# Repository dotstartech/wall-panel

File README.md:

# Wall Panel

Wall Panel is a 4-inch wall-mounted touch display panel powered by Raspberry Pi Compute Module 4 (CM4). It features a 720x720 IPS multitouch display and can be used as a Home Assistant dashboard or any other embedded display application.

## Display
We use this [display](https://www.alibaba.com/product-detail/Square-4-Inch-IPS-LCD-Screen_1601268288719.html), but touch variant. It is 4 lane MIPI with i2c touch controller. 
- Display driver: ST7703
- Touch driver: FT6336U

## Possible use cases
- **Home Assistant Dashboard**. Perfect for wall-mounted smart home control panels with full touch interaction and high-resolution display.
- **Information Display**. Show weather, calendar, news, or any other dynamic content in your home or office.
- **Control Panel**. Use as a centralized control interface for IoT devices, lighting, or home automation systems.
- **Embedded Display**. Build custom applications using the full power of Raspberry Pi OS or any Linux distribution on the CM4.

## List of features
- **720x720 IPS Display** with multitouch support
- **Raspberry Pi Compute Module 4** as the main brain
- **External RTC** for accurate timekeeping
- **USB-C** for data and power
- **USB-OTG** support for device mode
- **Action Button** for user interaction
- **WiFi** connectivity
- **40-pin GPIO Header** for Raspberry Pi compatibility
- **SD Card** slot for storage expansion
- **Micro HDMI** output for external displays
- **EEPROM Flashing** capability for firmware updates
- **Backplane Connector** for power and data from the wall and future PoE backplate support

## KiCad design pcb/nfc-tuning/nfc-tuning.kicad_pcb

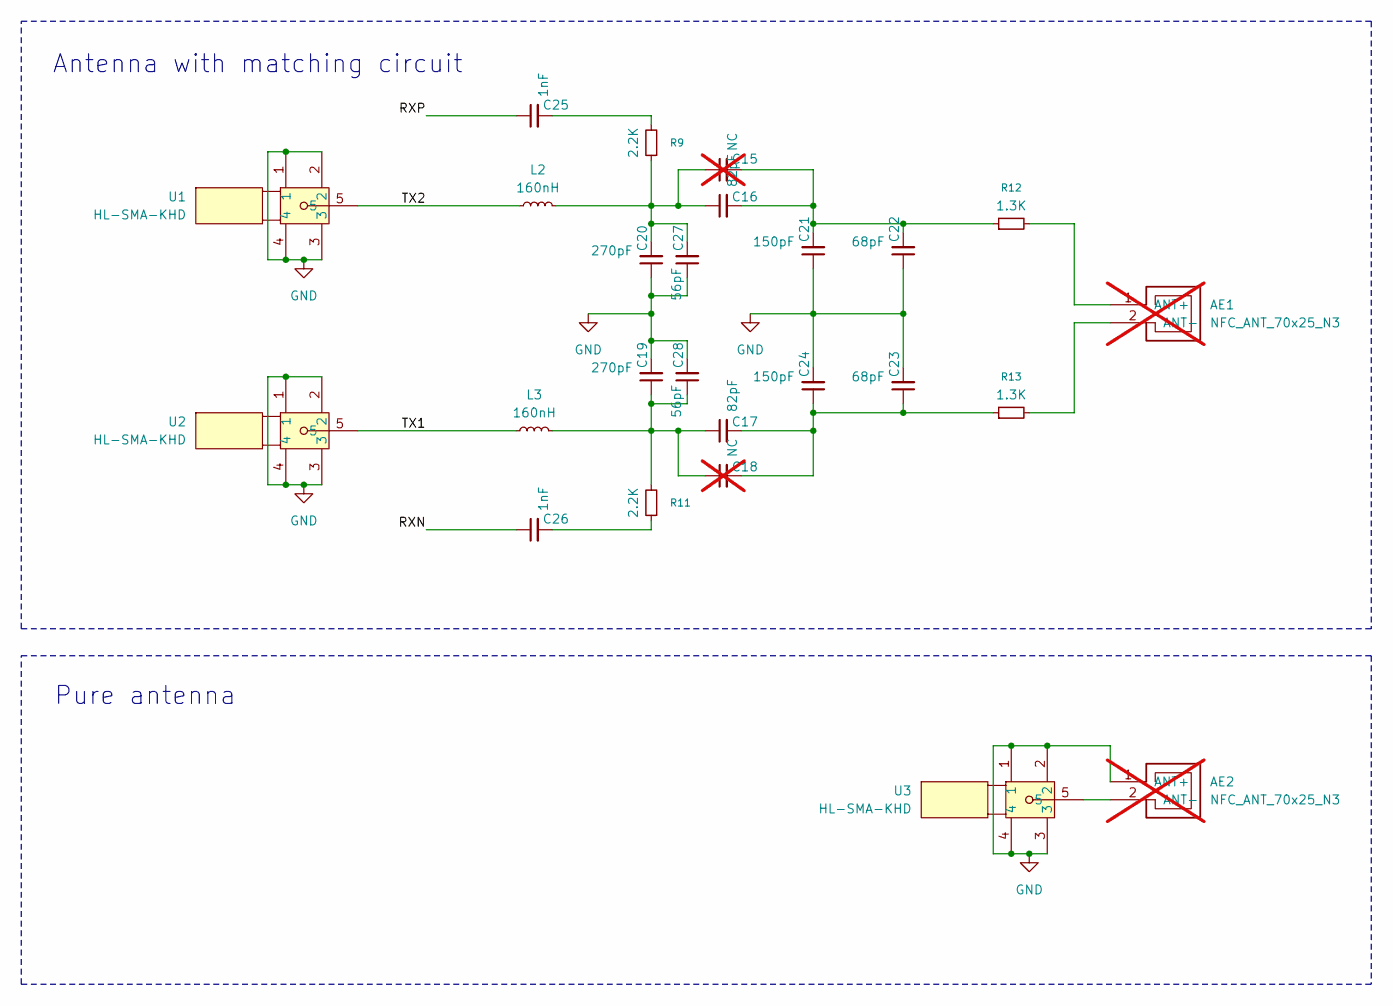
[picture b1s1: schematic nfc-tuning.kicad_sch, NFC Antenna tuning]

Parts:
AE1, AE2: NFC_ANT_70x25_N3; not fitted
C15, C18: NC; C_0402_1005Metric; not fitted
C16, C17: 82pF; C_0402_1005Metric; LCSC C162123
C19, C20: 270pF; C_0402_1005Metric; LCSC C882580
C21, C24: 150pF; C_0402_1005Metric; LCSC C237333
C22, C23: 68pF; C_0402_1005Metric; LCSC C2987942
C25, C26: 1nF; C_0402_1005Metric; LCSC C161523
C27, C28: 56pF; C_0402_1005Metric; LCSC C2189899
L2, L3: 160nH; L_0603_1608Metric; LCSC C437367
R9, R11: 2.2K; R_0402_1005Metric; LCSC C2906865
R12, R13: 1.3K; R_0402_1005Metric; LCSC C185455
U1, U2, U3: HL-SMA-KHD; SMA-TH_HL-SMA-KHD2; MPN HL-SMA-KHD; LCSC Part C19712120

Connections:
/RXN: C26.1
/RXP: C25.1
/TX1: L3.1, U2.5
/TX2: L2.1, U1.5
GND: AE2.1 (ANT+), AE2.2 (ANT-), C19.2, C20.1, C21.1, C22.1, C23.2, C24.2, C27.1, C28.2, U1.1, U1.2, U1.3, U1.4, U2.1, U2.2, U2.3, U2.4, U3.1, U3.2, U3.3, U3.4; also elsewhere on the board
unnamed: AE1.1 (ANT+), R12.2
unnamed: AE1.2 (ANT-), R13.2
unnamed: AE2.2 (ANT-), U3.5
unnamed: C15.1, C16.1, C20.2, C27.2, L2.2, R9.1
unnamed: C15.2, C16.2, C21.2, C22.2, R12.1
unnamed: C17.1, C18.1, C19.1, C28.1, L3.2, R11.2
unnamed: C17.2, C18.2, C23.1, C24.1, R13.1
unnamed: C25.2, R9.2
unnamed: C26.2, R11.1

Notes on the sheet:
Antenna with matching circuit
Pure antenna

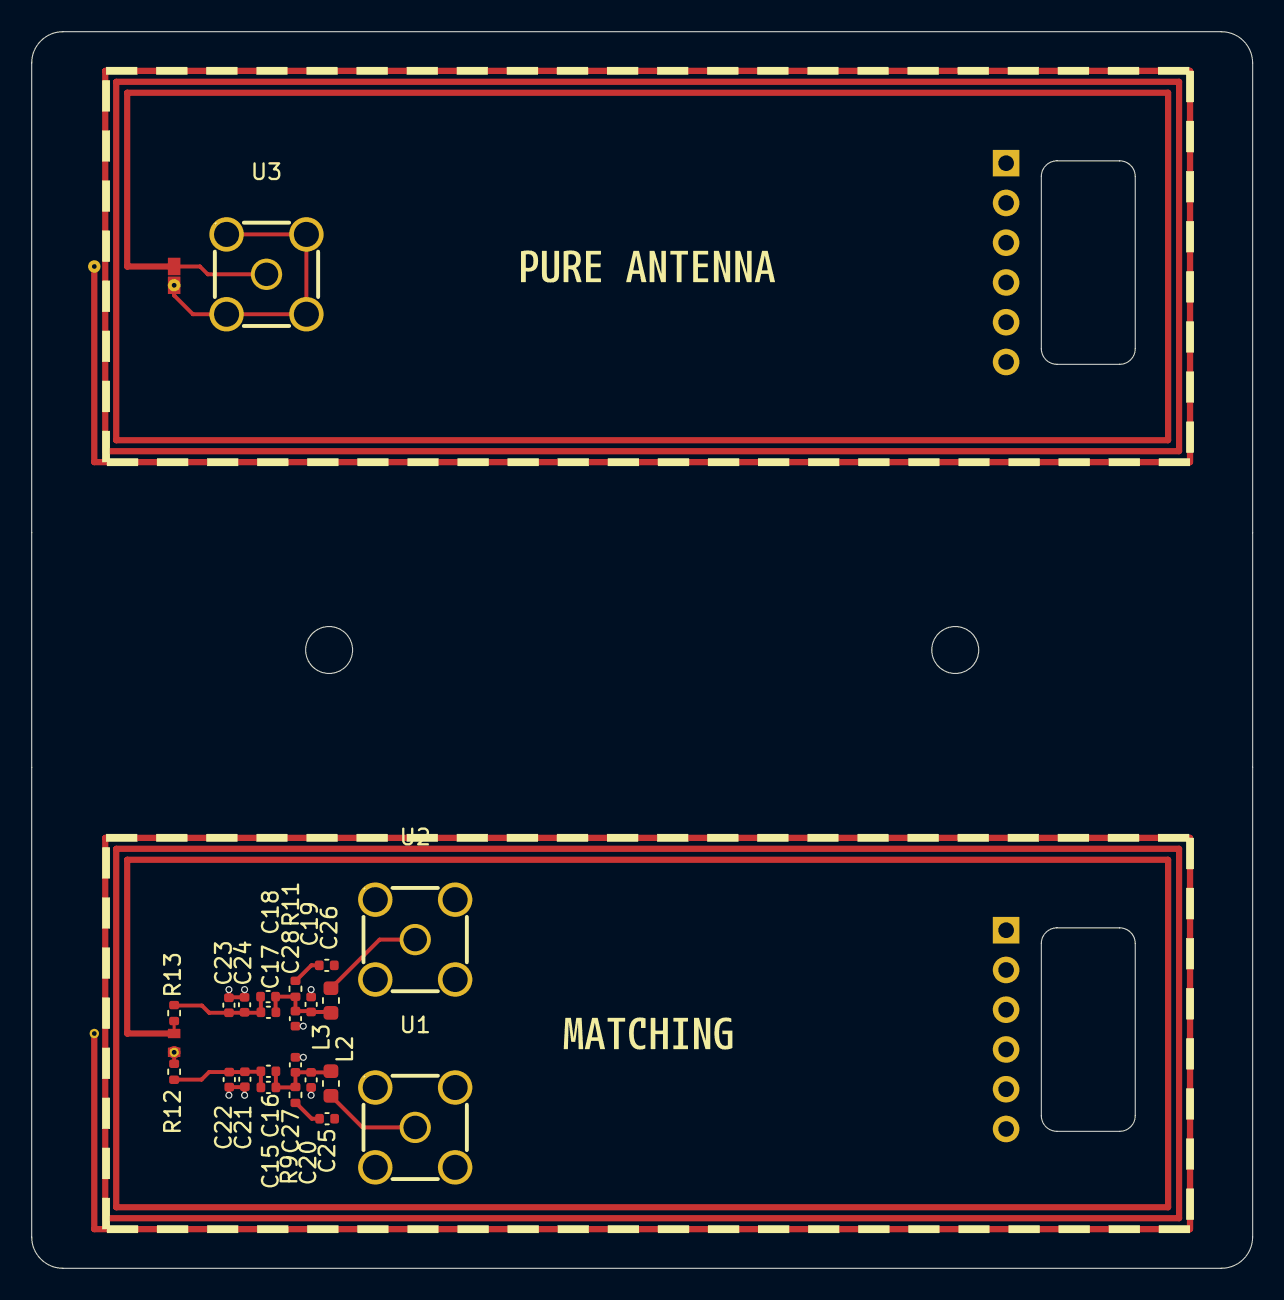
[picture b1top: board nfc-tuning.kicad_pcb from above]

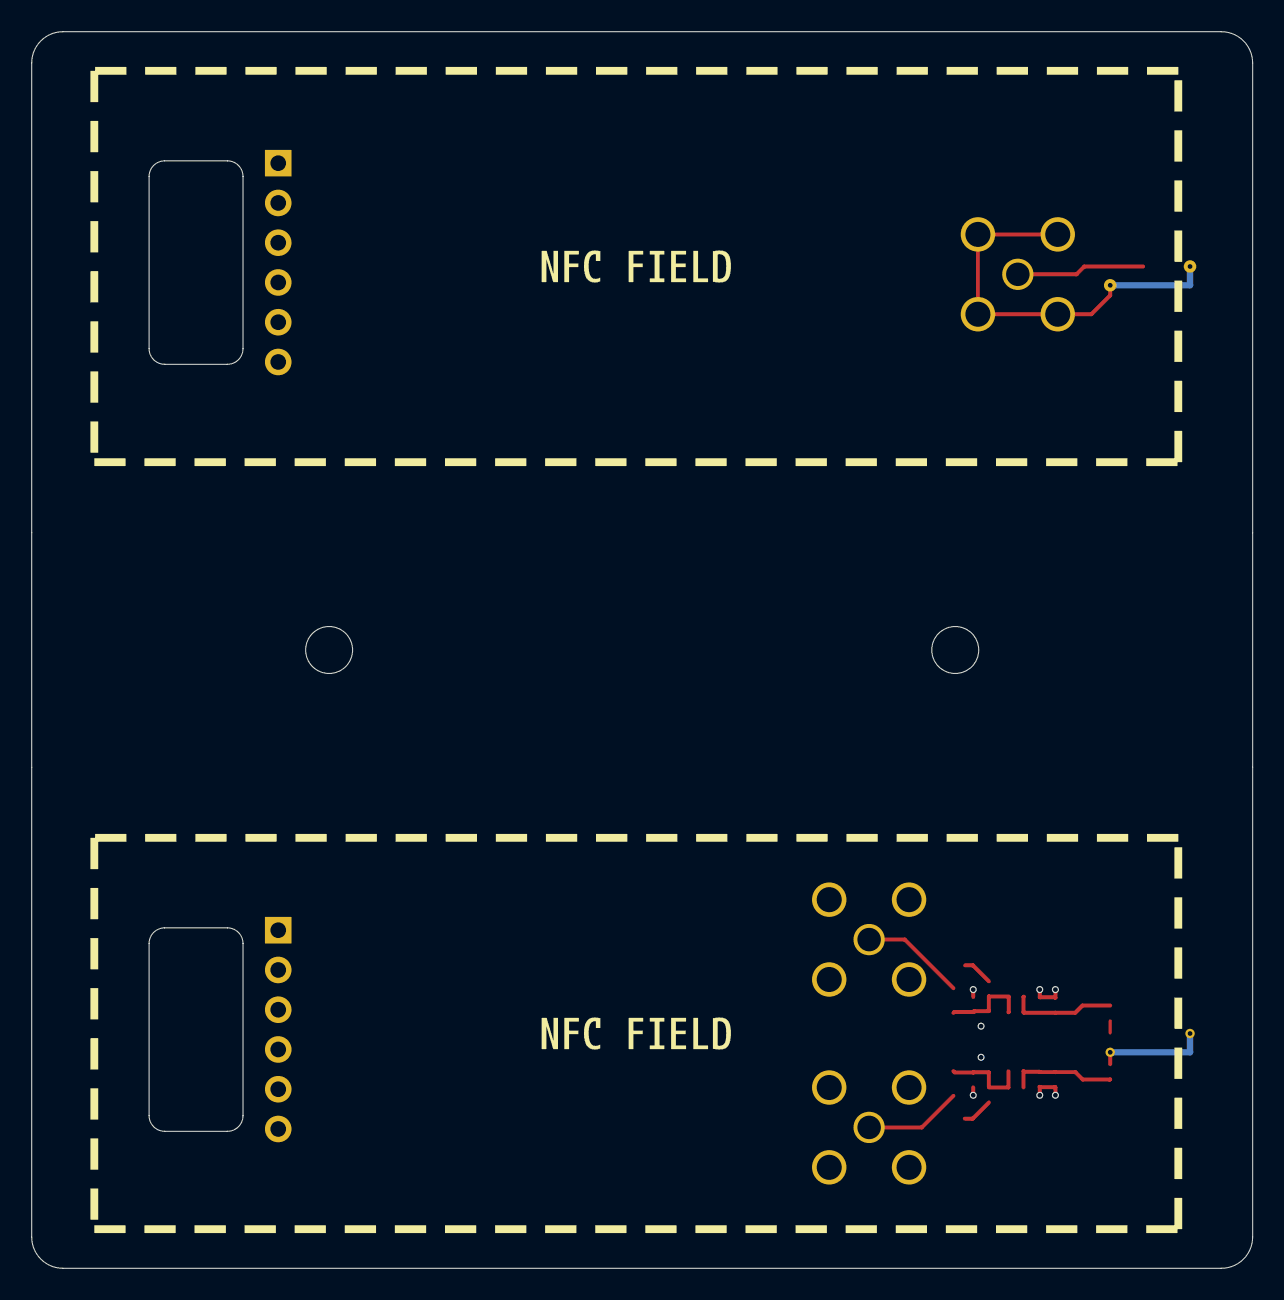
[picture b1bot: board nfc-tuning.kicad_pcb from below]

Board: 4 copper layers, 78.0 x 79.0 mm, 31 parts (2 on the bottom side), 12 nets.

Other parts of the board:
J5, J5#2: Mic Adafruit; SPH0645LM4H
kibuzzard-6A730F68: G***; kibuzzard-6A730F68
kibuzzard-6A730F73: G***; kibuzzard-6A730F73
kibuzzard-6A70487D, kibuzzard-6A70487D#2: G***; kibuzzard-6A70487D

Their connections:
GND: J5#2.2; also elsewhere on the board

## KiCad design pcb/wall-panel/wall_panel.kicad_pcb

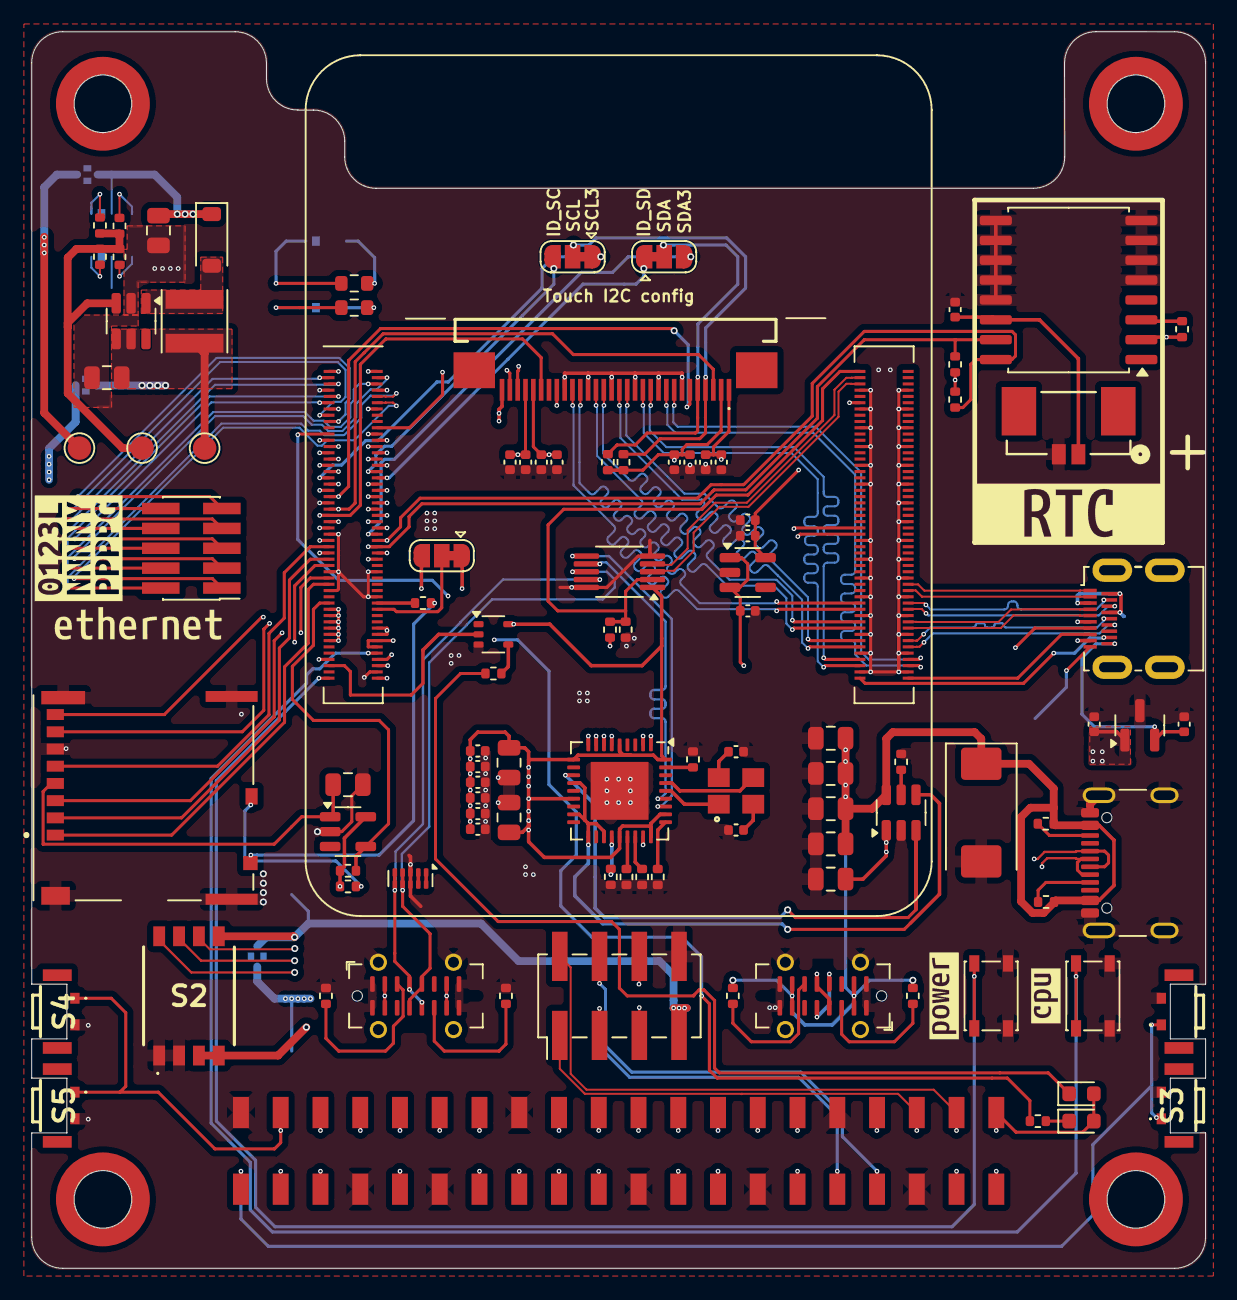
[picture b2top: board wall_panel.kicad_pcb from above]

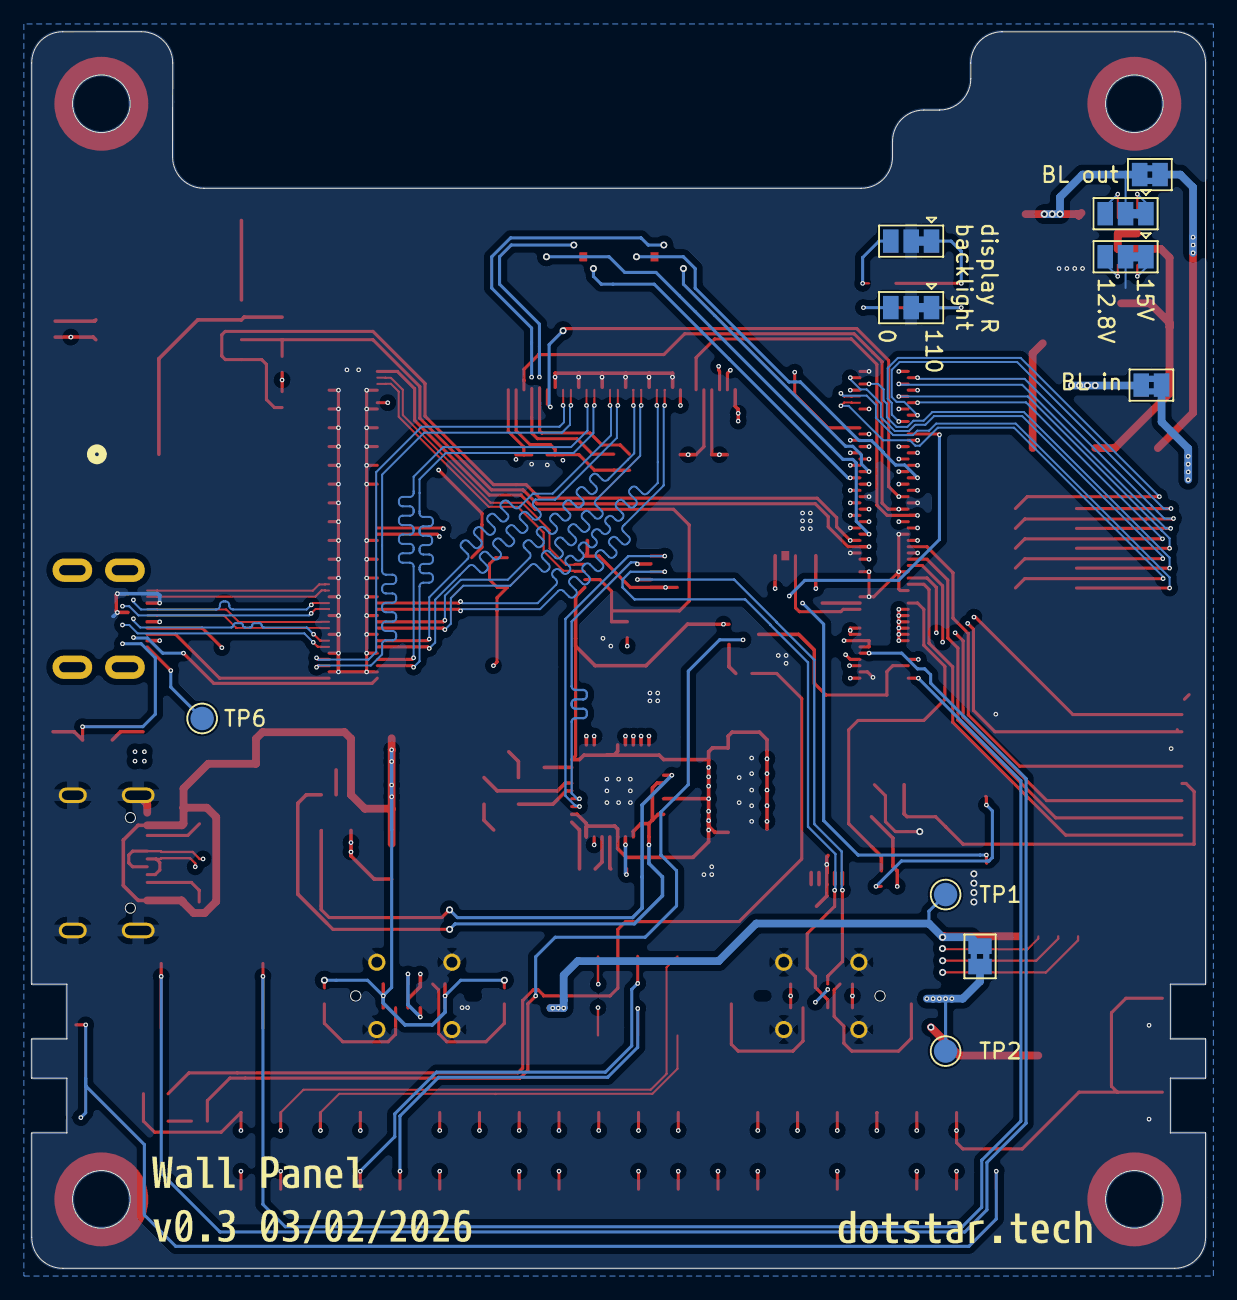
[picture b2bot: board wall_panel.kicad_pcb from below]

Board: 6 copper layers, 75.0 x 79.0 mm, 124 parts (13 on the bottom side), 142 nets.

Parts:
C1, C2: 27pF; C_0402_1005Metric
C3, C4, C11, C13, C14, C15, C16, C31: 10u; C_0805_2012Metric
C5, C6, C7, C8, C9, C10, C17, C18, C19, C22, C23, C24, C27, C28: 100n; C_0402_1005Metric
C12: 100uF; CP_EIA-7343-31_Kemet-D
C20, C21: 10uF; C_0402_1005Metric
C25, C26, C29, C30: 1uF; C_0402_1005Metric
C32, C33: 22uF; C_0805_2012Metric
D1: LED Green; LED_0603_1608Metric
D2: LED Red; LED_0603_1608Metric
D3: B5817W; D_SOD-123
H1, H2, H3, H4: MountingHole_Pad; 9774030151R
J1, J2: USB_C_Receptacle_USB2.0_14P; USB_C_Receptacle_G-Switch_GT-USB-7051x
J4: Conn_01x02_Socket; CONN02_533984002_MOL
J5: SFV30R-4STBE1HLF; SFV30R4STBE1HLF
J6: 690-019-298-412; HDMI_Micro-D_Molex_46765-1x01
J10: THD-20-R; PM254-2-20-WS-8.5
J15: THD-20-R; PinHeader_2x05_P1.27mm_Vertical_SMD
J16: Micro_SD_Card_Det; SDCARD_MOLEX_503398-1892
J17: USB_C_Receptacle_USB2.0_14P; USB_C_Receptacle_GCT_USB4105-xx-A_16P_TopMnt_Horizontal
J18: THD-20-R; PinHeader_2x04_P2.54mm_Vertical_SMD
JP1, JP3, JP4: GPIO reference; SolderJumper-3_P1.3mm_Bridged12_RoundedPad1.0x1.5mm
JP2: Jumper_2_Small_Bridged; SolderJumper-2_P1.3mm_Bridged2Bar_Pad1.0x1.5mm
JP5, JP6: SolderJumper_2_Bridged; SolderJumper-2_P1.3mm_Bridged2Bar_Pad1.0x1.5mm
JP7, JP8: 12.8/15V; SolderJumper-3_P1.3mm_Bridged12_Pad1.0x1.5mm
JP9, JP10: 0/110ohm; SolderJumper-3_P1.3mm_Bridged12_Pad1.0x1.5mm
L1: 10uH; L_Taiyo-Yuden_NR-40xx
Module1: ComputeModule4; Raspberry-Pi-4-Compute-Module
R1, R2, R14, R15: 2.2K 1%; R_0402_1005Metric
R3, R4, R5, R7: 36K 1%; R_0402_1005Metric
R6, R22: 12K 1%; R_0402_1005Metric
R8, R9: 5.1k; R_0402_1005Metric
R10, R12, R25, R26: 56K; R_0402_1005Metric
R11: 15K 1%; R_0402_1005Metric
R13, R18, R29: 10K; R_0402_1005Metric
R16, R19: 1k; R_0402_1005Metric
R17: 200K; R_0402_1005Metric
R20, R21: nf; R_0402_1005Metric
R23, R24: 4.7k; R_0402_1005Metric
R27, R28: 110; R_0603_1608Metric
R30: 240K; R_0402_1005Metric
S1, S3, S4, S5: SKSLLBE010
S2: 218-4LPSTRF; 2184LPSTRF
SW1: power reset; SW_SPST_PTS810
SW2: cpu reset; SW_SPST_PTS810
TP1, TP2, TP6: TestPoint; TestPoint_Pad_D1.5mm
TP3: boost in; TestPoint_Pad_D1.5mm
TP4: boost out; TestPoint_Pad_D1.5mm
TP5: boost fb; TestPoint_Pad_D1.5mm
U1: FSUSB42MUX; MSOP-10_3x3mm_P0.5mm
U2: USB2514B-I/M2; QFN-36-1EP_6x6mm_P0.5mm_EP3.7x3.7mm
U3: TPD4EUSB30; USON-10_2.5x1.0mm_P0.5mm
U4: AP22653W6; SOT-23-6
U5: DS3231M; SOIC-16W_7.5x10.3mm_P1.27mm
U6: RT9742SNGV; SOT-23
U7: LP5907MFX-2.8; SOT-23-5
U9: 74LVC1G07SE-7; SOT-353_SC-70-5
U10: RT9742GGJ5; SOT-23-5
U11: MT3608; SOT-23-6
Y1: ABM8G-24.000MHZ-18-D2Y-T; ABM8G
kibuzzard-68AB3D2F: G***; kibuzzard-68AB3D2F
kibuzzard-68AC3314: G***; kibuzzard-68AC3314
kibuzzard-68F10A66: G***; kibuzzard-68F10A66
kibuzzard-68F655E1: G***; kibuzzard-68F655E1
kibuzzard-68F655EA: G***; kibuzzard-68F655EA
kibuzzard-68F10531: G***; kibuzzard-68F10531
kibuzzard-6981E919: G***; kibuzzard-6981E919
kibuzzard-6984C46F: G***; kibuzzard-6984C46F

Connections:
+2.8v: C21.2, C22.2, C24.1, C26.1, C28.1, C30.1, J5.4 (VCI_4), J5.5 (IOVCC_5), U7.5 (OUT)
+3.3V: C3.1, C4.1, C5.1, C6.1, C7.1, C8.1, C9.1, C10.1, C20.2, C23.1, C25.1, C27.1, C29.1, D1.2 (A), D2.2 (A), J5.29 (TP_VCI_29), J5.30 (TP_IOVCC_30), J10.1, J10.17, JP1.1 (A), Module1.84 (+3.3v_(Output)), Module1.86 (+3.3v_(Output)), R13.2, R14.1, R15.1, R20.1, R22.1, R23.1, R24.1, U1.1 (VCC), U2.5 (VDDA33), U2.10 (VDDA33), U2.15 (VDD33), U2.23 (VDD33), U2.27 (VBUS_DET), U2.29 (VDDA33), U2.36 (VDDA33), U5.2 (VCC), U7.1 (IN), U7.3 (EN), U9.5 (VCC), U10.5 (IN)
+5V: C11.1, C18.1, J10.2, J10.4, JP2.2 (B), JP5.1 (A), Module1.77 (+5v_(Input)), Module1.79 (+5v_(Input)), Module1.81 (+5v_(Input)), Module1.83 (+5v_(Input)), Module1.85 (+5v_(Input)), Module1.87 (+5v_(Input)), TP2.1, U4.1 (IN), U6.1 (IN)
/CM4_GPIO ( Ethernet, GPIO, SDCARD)/+1.8v: JP1.3 (B), Module1.88 (+1.8v_(Output)), Module1.90 (+1.8v_(Output))
/CM4_GPIO ( Ethernet, GPIO, SDCARD)/EEPROM_nWP: Module1.20 (EEPROM_nWP), S2.8
/CM4_GPIO ( Ethernet, GPIO, SDCARD)/ETH_LEDG: J15.9, Module1.17 (Ethernet_nLED2(3.3v))
/CM4_GPIO ( Ethernet, GPIO, SDCARD)/ETH_LEDY: J15.10, Module1.15 (Ethernet_nLED3(3.3v))
/CM4_GPIO ( Ethernet, GPIO, SDCARD)/GLOBAL_EN: Module1.99 (Global_EN), SW1.1
/CM4_GPIO ( Ethernet, GPIO, SDCARD)/GPIO2: J10.3, J18.2, Module1.58 (GPIO2), R23.2, U5.15 (SDA)
/CM4_GPIO ( Ethernet, GPIO, SDCARD)/GPIO3: J10.5, J18.1, Module1.56 (GPIO3), R24.2, U5.16 (SCL)
/CM4_GPIO ( Ethernet, GPIO, SDCARD)/GPIO4: J10.7, JP3.3 (B), Module1.54 (GPIO4)
/CM4_GPIO ( Ethernet, GPIO, SDCARD)/GPIO5: J10.29, JP4.3 (B), Module1.34 (GPIO5)
/CM4_GPIO ( Ethernet, GPIO, SDCARD)/GPIO6: J10.31, Module1.30 (GPIO6)
/CM4_GPIO ( Ethernet, GPIO, SDCARD)/GPIO7: J10.26, Module1.37 (GPIO7)
/CM4_GPIO ( Ethernet, GPIO, SDCARD)/GPIO8: J10.24, Module1.39 (GPIO8)
/CM4_GPIO ( Ethernet, GPIO, SDCARD)/GPIO9: J10.21, Module1.40 (GPIO9)
/CM4_GPIO ( Ethernet, GPIO, SDCARD)/GPIO10: J10.19, Module1.44 (GPIO10)
/CM4_GPIO ( Ethernet, GPIO, SDCARD)/GPIO11: J10.23, Module1.38 (GPIO11)
/CM4_GPIO ( Ethernet, GPIO, SDCARD)/GPIO12: J5.8, J10.32, Module1.31 (GPIO12)
/CM4_GPIO ( Ethernet, GPIO, SDCARD)/GPIO13: J10.33, Module1.28 (GPIO13)
/CM4_GPIO ( Ethernet, GPIO, SDCARD)/GPIO14: J10.8, J18.4, Module1.55 (GPIO14)
/CM4_GPIO ( Ethernet, GPIO, SDCARD)/GPIO15: J10.10, J18.3, Module1.51 (GPIO15)
/CM4_GPIO ( Ethernet, GPIO, SDCARD)/GPIO16: J10.36, Module1.29 (GPIO16)
/CM4_GPIO ( Ethernet, GPIO, SDCARD)/GPIO17: J10.11, Module1.50 (GPIO17)
/CM4_GPIO ( Ethernet, GPIO, SDCARD)/GPIO18: J10.12, Module1.49 (GPIO18)
/CM4_GPIO ( Ethernet, GPIO, SDCARD)/GPIO19: J10.35, Module1.26 (GPIO19)
/CM4_GPIO ( Ethernet, GPIO, SDCARD)/GPIO20: J10.38, Module1.27 (GPIO20)
/CM4_GPIO ( Ethernet, GPIO, SDCARD)/GPIO21: J10.40, Module1.25 (GPIO21), S1.1, S3.1
/CM4_GPIO ( Ethernet, GPIO, SDCARD)/GPIO22: J10.15, Module1.46 (GPIO22)
/CM4_GPIO ( Ethernet, GPIO, SDCARD)/GPIO23: J5.6 (RESET_6), J10.16, Module1.47 (GPIO23)
/CM4_GPIO ( Ethernet, GPIO, SDCARD)/GPIO24: J5.28 (TP_RESET_28), J10.18, Module1.45 (GPIO24)
/CM4_GPIO ( Ethernet, GPIO, SDCARD)/GPIO25: J5.25 (TP_INT_25), J10.22, Module1.41 (GPIO25)
/CM4_GPIO ( Ethernet, GPIO, SDCARD)/GPIO26: J10.37, Module1.24 (GPIO26), S4.1, S5.1
/CM4_GPIO ( Ethernet, GPIO, SDCARD)/GPIO27: J10.13, Module1.48 (GPIO27)
/CM4_GPIO ( Ethernet, GPIO, SDCARD)/GPIO_VREF: JP1.2 (C), Module1.78 (GPIO_VREF(1.8v/3.3v_Input))
/CM4_GPIO ( Ethernet, GPIO, SDCARD)/ID_SC: J10.28, JP4.1 (A), Module1.35 (ID_SC)
/CM4_GPIO ( Ethernet, GPIO, SDCARD)/ID_SD: J10.27, JP3.1 (A), Module1.36 (ID_SD)
/CM4_GPIO ( Ethernet, GPIO, SDCARD)/OTG_MODE_SW1: R2.1, S2.6
/CM4_GPIO ( Ethernet, GPIO, SDCARD)/RUN_PG: Module1.92 (RUN_PG), SW2.1
/CM4_GPIO ( Ethernet, GPIO, SDCARD)/Reserved: Module1.76 (Reserved), R21.1
/CM4_GPIO ( Ethernet, GPIO, SDCARD)/SD_CLK: J16.5 (CLK), Module1.57 (SD_CLK)
/CM4_GPIO ( Ethernet, GPIO, SDCARD)/SD_CMD: J16.3 (CMD), Module1.62 (SD_CMD)
/CM4_GPIO ( Ethernet, GPIO, SDCARD)/SD_DAT0: J16.7 (DAT0), Module1.63 (SD_DAT0)
/CM4_GPIO ( Ethernet, GPIO, SDCARD)/SD_DAT1: J16.8 (DAT1), Module1.67 (SD_DAT1)
/CM4_GPIO ( Ethernet, GPIO, SDCARD)/SD_DAT2: J16.1 (DAT2), Module1.69 (SD_DAT2)
/CM4_GPIO ( Ethernet, GPIO, SDCARD)/SD_DAT3: J16.2 (DAT3/CD), Module1.61 (SD_DAT3)
/CM4_GPIO ( Ethernet, GPIO, SDCARD)/SD_PWR: C31.1, J16.4 (VDD), U10.1 (OUT)
/CM4_GPIO ( Ethernet, GPIO, SDCARD)/SD_PWR_ON: Module1.75 (SD_PWR_ON), R22.2, U10.4 (EN)
/CM4_GPIO ( Ethernet, GPIO, SDCARD)/TRD0_N: J15.2, Module1.10 (Ethernet_Pair0_N)
/CM4_GPIO ( Ethernet, GPIO, SDCARD)/TRD0_P: J15.1, Module1.12 (Ethernet_Pair0_P)
/CM4_GPIO ( Ethernet, GPIO, SDCARD)/TRD1_N: J15.4, Module1.6 (Ethernet_Pair1_N)
/CM4_GPIO ( Ethernet, GPIO, SDCARD)/TRD1_P: J15.3, Module1.4 (Ethernet_Pair1_P)
/CM4_GPIO ( Ethernet, GPIO, SDCARD)/TRD2_N: J15.6, Module1.9 (Ethernet_Pair2_N)
/CM4_GPIO ( Ethernet, GPIO, SDCARD)/TRD2_P: J15.5, Module1.11 (Ethernet_Pair2_P)
/CM4_GPIO ( Ethernet, GPIO, SDCARD)/TRD3_N: J15.8, Module1.5 (Ethernet_Pair3_N)
/CM4_GPIO ( Ethernet, GPIO, SDCARD)/TRD3_P: J15.7, Module1.3 (Ethernet_Pair3_P)
/CM4_GPIO ( Ethernet, GPIO, SDCARD)/nActivity_LED: Module1.21 (PI_nLED_Activity), R16.2
/CM4_GPIO ( Ethernet, GPIO, SDCARD)/nPWR_LED: Module1.95 (nPI_LED_PWR), U9.2
/CM4_GPIO ( Ethernet, GPIO, SDCARD)/nRPIBOOT: Module1.93 (nRPIBOOT), S2.7
/CM4_HighSpeed/BACKLIGHT_POWER: J5.1 (LEDA_1), JP6.2 (B), TP4.1
/CM4_HighSpeed/DSI1_C_N: J5.17 (CLKN_17), Module1.187 (DSI1_C_N)
/CM4_HighSpeed/DSI1_C_P: J5.16 (CLKP_16), Module1.189 (DSI1_C_P)
/CM4_HighSpeed/DSI1_D0_N: J5.11 (MIPI_0N_11), Module1.175 (DSI1_D0_N)
/CM4_HighSpeed/DSI1_D0_P: J5.10 (MIPI_0P_10), Module1.177 (DSI1_D0_P)
/CM4_HighSpeed/DSI1_D1_N: J5.14 (MIPI_1N_14), Module1.181 (DSI1_D1_N)
/CM4_HighSpeed/DSI1_D1_P: J5.13 (MIPI_1P_13), Module1.183 (DSI1_D1_P)
/CM4_HighSpeed/DSI1_D2_N: J5.20 (MIPI_2N__20), Module1.193 (DSI1_D2_N)
/CM4_HighSpeed/DSI1_D2_P: J5.19 (MIPI_2P_19), Module1.195 (DSI1_D2_P)
/CM4_HighSpeed/DSI1_D3_N: J5.23 (MIPI_3N_23), Module1.194 (DSI1_D3_N)
/CM4_HighSpeed/DSI1_D3_P: J5.22 (MIPI_3P_22), Module1.196 (DSI1_D3_P)
/CM4_HighSpeed/HDMI0_CEC: J6.13 (CEC), Module1.151 (HDMI0_CEC)
/CM4_HighSpeed/HDMI0_CK_N: J6.12 (CK-), Module1.190 (HDMI0_CLK_N)
/CM4_HighSpeed/HDMI0_CK_P: J6.10 (CK+), Module1.188 (HDMI0_CLK_P)
/CM4_HighSpeed/HDMI0_D0_N: J6.9 (D0-), Module1.184 (HDMI0_TX0_N)
/CM4_HighSpeed/HDMI0_D0_P: J6.7 (D0+), Module1.182 (HDMI0_TX0_P)
/CM4_HighSpeed/HDMI0_D1_N: J6.6 (D1-), Module1.178 (HDMI0_TX1_N)
/CM4_HighSpeed/HDMI0_D1_P: J6.4 (D1+), Module1.176 (HDMI0_TX1_P)
/CM4_HighSpeed/HDMI0_D2_N: J6.3 (D2-), Module1.172 (HDMI0_TX2_N)
/CM4_HighSpeed/HDMI0_D2_P: J6.1 (D2+), Module1.170 (HDMI0_TX2_P)
/CM4_HighSpeed/HDMI0_HOTPLUG: J6.19 (HPD/HEAC-), Module1.153 (HDMI0_HOTPLUG), TP6.1
/CM4_HighSpeed/HDMI0_SCL: J6.15 (SCL), Module1.200 (HDMI0_SCL)
/CM4_HighSpeed/HDMI0_SDA: J6.16 (SDA), Module1.199 (HDMI0_SDA)
/CM4_HighSpeed/HDMI_5v: C19.1, J6.18 (+5V), U6.2 (OUT)
/CM4_HighSpeed/TOUCH_SCL: J5.27 (TP_SCL_27), JP4.2 (C), R15.2
/CM4_HighSpeed/TOUCH_SDA: J5.26 (TP_SDA_26), JP3.2 (C), R14.2
/CM4_HighSpeed/USB2_N: Module1.103 (USB2_N), U1.4 (D_N)
/CM4_HighSpeed/USB2_P: Module1.105 (USB2_P), U1.3 (D_P)
/CM4_HighSpeed/USBOTG_ID: Module1.101 (USB_OTG_ID), R1.1, R2.2, U1.2 (SEL)
/RTC , Wakeup, FAN/nRTC_INT: R13.1, U5.3 (~INT/SQW)
/USB2-HUB/HD1_N: J2.A7 (D-), J2.B7 (D-), U2.1 (USBDM_DN1/PRT_DIS_M1)
/USB2-HUB/HD1_P: J2.A6 (D+), J2.B6 (D+), U2.2 (USBDP_DN1/PRT_DIS_P1)
/USB2-HUB/HD3_N: J18.5, U2.6 (USBDM_DN3/PRT_DIS_M3)
/USB2-HUB/HD3_P: J18.6, U2.7 (USBDP_DN3/PRT_DIS_P3)
/USB2-HUB/HD4_N: J17.A7 (D-), J17.B7 (D-), U2.8 (USBDM_DN4/PRT_DIS_M4)
/USB2-HUB/HD4_P: J17.A6 (D+), J17.B6 (D+), U2.9 (USBDP_DN4/PRT_DIS_P4)
/USB2-HUB/OTG_5V_IN: J1.A4 (VBUS), J1.A9 (VBUS), J1.B4 (VBUS), J1.B9 (VBUS), S2.3, S2.4
/USB2-HUB/PWR1: U2.12 (PRTPWR1/BC_EN1), U4.3 (EN)
/USB2-HUB/USBD_N: J1.A7 (D-), J1.B7 (D-), U1.8 (HSD1_M), U3.4 (D2+), U3.7
/USB2-HUB/USBD_P: J1.A6 (D+), J1.B6 (D+), U1.9 (HSD1_P), U3.5 (D2-), U3.6
/USB2-HUB/USBH_N: U1.6 (HSD0_M), U2.30 (USBDM_UP)
/USB2-HUB/USBH_P: U1.7 (HSD0_P), U2.31 (USBDP_UP)
/USB2-HUB/VBUS_OUT: C12.1, C13.1, C14.1, C15.1, C16.1, J2.A4 (VBUS), J2.A9 (VBUS), J2.B4 (VBUS), J2.B9 (VBUS), J17.A4 (VBUS), J17.A9 (VBUS), J17.B4 (VBUS), J17.B9 (VBUS), R10.2, R12.2, R25.2, R26.2, U4.6 (OUT)
/USB2-HUB/nOCS1: U2.13 (OCS_N1), U2.17 (OCS_N2), U2.19 (OCS_N3), U2.21 (OCS_N4), U4.4 (nFault)
/VBUS: J18.7, JP2.1 (A), S2.5, TP1.1
/nEXTRST: Module1.100 (nEXTRST), U2.26 (RESET_N)
GND: C1.2, C2.2, C3.2, C4.2, C5.2, C6.2, C7.2, C8.2, C9.2, C10.2, C11.2, C12.2, C13.2, C14.2, C15.2, C16.2, C17.2, C18.2, C19.2, C20.1, C21.1, C22.1, C23.2, C24.2, C25.2, C26.2, C27.2, C28.2, C29.2, C30.2, C31.2, C32.2, C33.2, J1.A1 (GND), J1.A12 (GND), J1.B1 (GND), J1.B12 (GND), J1.S1 (SHIELD), J2.A1 (GND), J2.A12 (GND), J2.B1 (GND), J2.B12 (GND), J2.S1 (SHIELD), J4.2, J5.9 (GND_9), J5.12 (GND_12), J5.15 (GND_15), J5.18 (GND_18), J5.21 (GND_21), J5.24 (GND_24), J6.2 (D2S), J6.5 (D1S), J6.8 (D0S), J6.11 (CKS), J6.17 (GND), J10.6, J10.9, J10.14, J10.20, J10.25, J10.30, J10.34, J10.39, J16.6 (VSS), J16.11 (SHIELD), J17.A1 (GND), J17.A12 (GND), J17.B1 (GND), J17.B12 (GND), J17.S1 (SHIELD), J18.8, JP8.2 (C), JP9.2 (C), JP10.2 (C), Module1.1 (GND), Module1.2 (GND), Module1.7 (GND), Module1.8 (GND), Module1.13 (GND), Module1.14 (GND), Module1.22 (GND), Module1.23 (GND), Module1.32 (GND), Module1.33 (GND), Module1.42 (GND), Module1.43 (GND), Module1.52 (GND), Module1.53 (GND), Module1.59 (GND), Module1.60 (GND), Module1.65 (GND), Module1.66 (GND), Module1.71 (GND), Module1.74 (GND), Module1.98 (GND), Module1.107 (GND), Module1.108 (GND), Module1.113 (GND), Module1.114 (GND), Module1.119 (GND), Module1.120 (GND), Module1.125 (GND), Module1.126 (GND), Module1.131 (GND), Module1.132 (GND), Module1.137 (GND), Module1.138 (GND), Module1.144 (GND), Module1.150 (GND), Module1.155 (GND), Module1.156 (GND), Module1.161 (GND), Module1.162 (GND), Module1.167 (GND), Module1.168 (GND), Module1.173 (GND), Module1.174 (GND), Module1.179 (GND), Module1.180 (GND), Module1.185 (GND), Module1.186 (GND), Module1.191 (GND), Module1.192 (GND), Module1.197 (GND), Module1.198 (GND), R1.2, R3.2, R4.2, R5.2, R6.1, R7.2, R8.1, R9.1, R11.2, S1.2, S2.1, S2.2, S3.2, S4.2, S5.2, SW1.2, SW2.2, U1.5 (GND), U1.10 (nOE), U2.37 (VSS), U3.3 (GND), U3.8 (GND), U4.2 (GND), U5.5 (GND), U5.6 (GND), U5.7 (GND), U5.8 (GND), U5.9 (GND), U5.10 (GND), U5.11 (GND), U5.12 (GND), U5.13 (GND), U6.3 (GND), U7.2 (GND), U9.3 (GND), U10.2 (GND), U11.2 (GND)
unnamed: D1.1 (K), R16.1
unnamed: D2.1 (K), R19.1
unnamed: D3.2 (A), L1.2, U11.1 (SW)
unnamed: C32.1, D3.1 (K), JP6.1 (A), JP7.2 (C)
unnamed: J1.A5 (CC1), R9.2
unnamed: J1.B5 (CC2), R8.2
unnamed: J2.A5 (CC1), R10.1
unnamed: J2.B5 (CC2), R12.1
unnamed: C17.1, J4.1, U5.14 (VBAT)
unnamed: J5.2 (LEDK1_2), JP10.3 (B), R28.2
unnamed: J5.3 (LEDK2_3), JP9.3 (B), R27.2
unnamed: J16.10 (DET_A), R20.2
unnamed: J16.9 (DET_B), R21.2
unnamed: J17.A5 (CC1), R25.1
unnamed: J17.B5 (CC2), R26.1
unnamed: C33.1, JP5.2 (B), L1.1, TP3.1, U11.4 (EN), U11.5 (IN)
unnamed: JP7.1 (A), R30.2
unnamed: JP7.3 (B), R17.2
unnamed: JP8.1 (A), R29.1
unnamed: JP8.3 (B), R18.1
unnamed: JP9.1 (A), R27.1
unnamed: JP10.1 (A), R28.1
unnamed: R19.2, U9.4
unnamed: R7.1, U2.25 (HS_IND/CFG_SEL1)
unnamed: R6.2, U2.35 (RBIAS)
unnamed: R3.1, U2.24 (SCL/SMBCLK/CFG_SEL0)
unnamed: R4.1, U2.22 (SDA/SMBDATA/NON_REM1)
unnamed: R5.1, U2.28 (SUSP_IND/LOCAL_PWR/NON_REM0)
unnamed: U2.33 (XTALIN/CLKIN), Y1.3 (XTAL_2)
unnamed: U2.32 (XTALOUT), Y1.1 (XTAL_1)
unnamed: U3.1 (D1+), U3.10
unnamed: U3.2 (D1-), U3.9
unnamed: R11.1, U4.5 (ILIM)
unnamed: R17.1, R18.2, R29.2, R30.1, TP5.1, U11.3 (FB)
unnamed: C2.1, Y1.2 (GND_1)
unnamed: C1.1, Y1.4 (GND_2)
